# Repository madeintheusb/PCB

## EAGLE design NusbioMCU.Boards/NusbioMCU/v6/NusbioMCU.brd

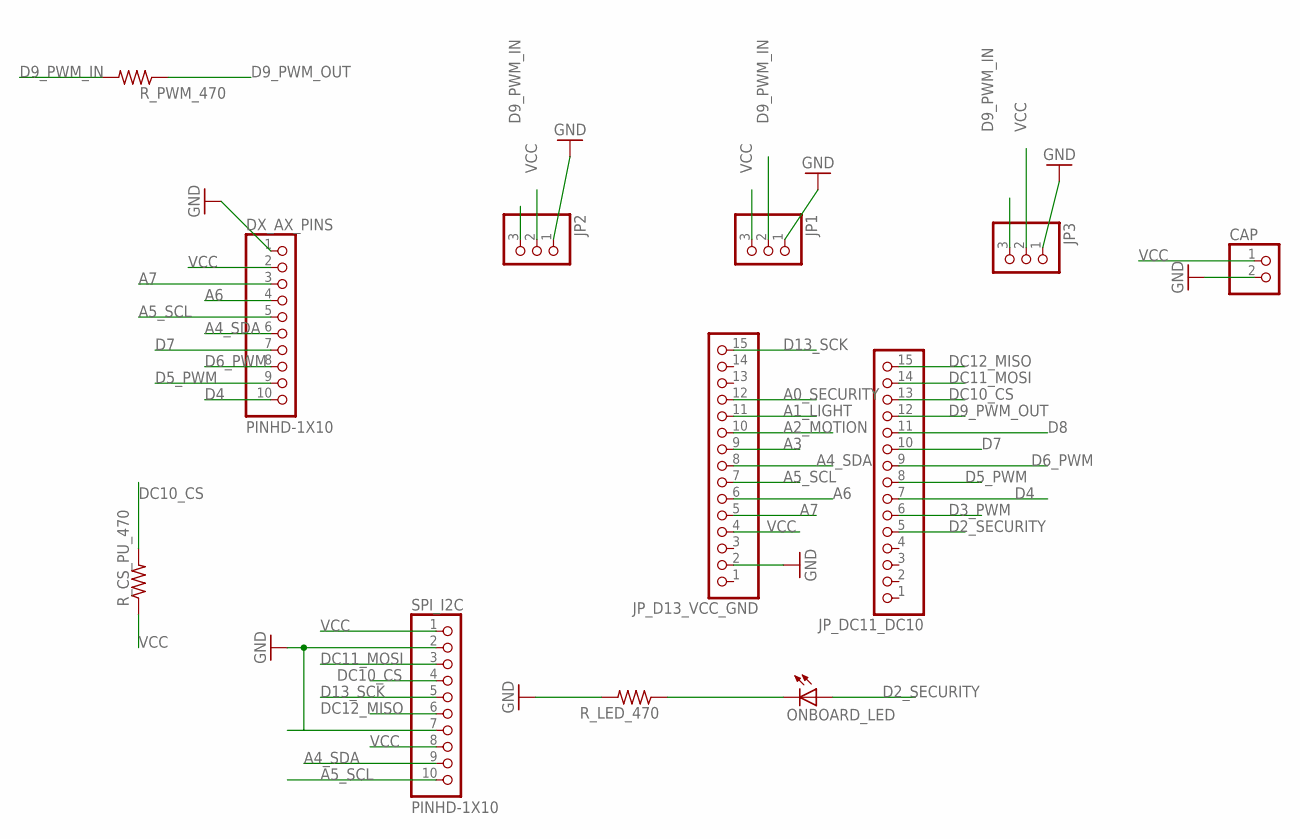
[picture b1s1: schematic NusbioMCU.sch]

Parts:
CAP: PINHD-1X2; 1X02
DX_AX_PINS: PINHD-1X10; 1X10-BIG
JP1, JP2, JP3: PINHD-1X3; 1X03
JP_D13_VCC_GND: PINHD-1X15; 1X15
JP_DC11_DC10: PINHD-1X15; 1X15
ONBOARD_LED: LEDSMT1206; 1206
R_CS_PU_470: R-US_R1206; R1206
R_LED_470: R-US_R1206; R1206
R_PWM_470: R-US_R1206; R1206
SPI_I2C: PINHD-1X10; 1X10-BIG

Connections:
A0_SECURITY: JP_D13_VCC_GND.12
A1_LIGHT: JP_D13_VCC_GND.11
A2_MOTION: JP_D13_VCC_GND.10
A3: JP_D13_VCC_GND.9
A4_SDA: DX_AX_PINS.6, JP_D13_VCC_GND.8, SPI_I2C.9
A5_SCL: DX_AX_PINS.5, JP_D13_VCC_GND.7, SPI_I2C.10
A6: DX_AX_PINS.4, JP_D13_VCC_GND.6
A7: DX_AX_PINS.3, JP_D13_VCC_GND.5
D2_SECURITY: JP_DC11_DC10.5, ONBOARD_LED.A
D3_PWM: JP_DC11_DC10.6
D4: DX_AX_PINS.10, JP_DC11_DC10.7
D5_PWM: DX_AX_PINS.9, JP_DC11_DC10.8
D6_PWM: DX_AX_PINS.8, JP_DC11_DC10.9
D7: DX_AX_PINS.7, JP_DC11_DC10.10
D8: JP_DC11_DC10.11
D9_PWM_IN: JP1.2, JP2.3, JP3.3, R_PWM_470.2
D9_PWM_OUT: JP_DC11_DC10.12, R_PWM_470.1
D13_SCK: JP_D13_VCC_GND.15, SPI_I2C.5
DC10_CS: JP_DC11_DC10.13, R_CS_PU_470.2, SPI_I2C.4
DC11_MOSI: JP_DC11_DC10.14, SPI_I2C.3
DC12_MISO: JP_DC11_DC10.15, SPI_I2C.6
GND: CAP.2, DX_AX_PINS.1, JP1.1, JP2.1, JP3.1, JP_D13_VCC_GND.2, R_LED_470.2, SPI_I2C.2, SPI_I2C.7
unnamed: ONBOARD_LED.C, R_LED_470.1
VCC: CAP.1, DX_AX_PINS.2, JP1.3, JP2.2, JP3.2, JP_D13_VCC_GND.4, R_CS_PU_470.1, SPI_I2C.1, SPI_I2C.8

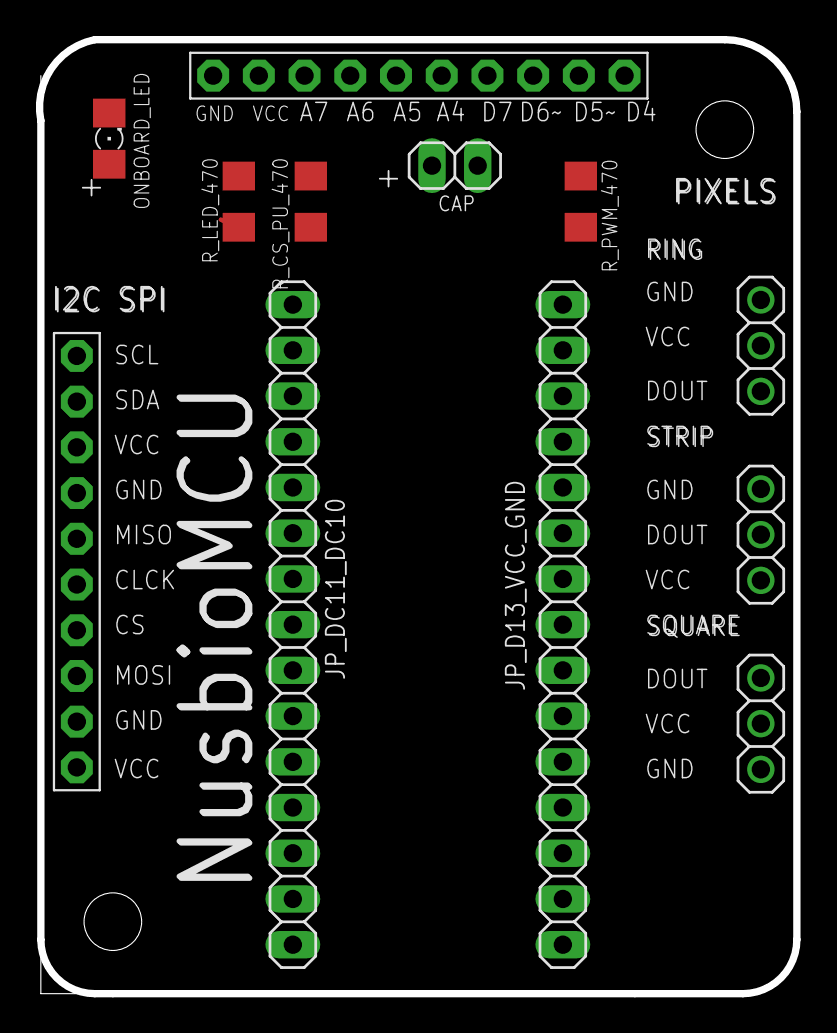
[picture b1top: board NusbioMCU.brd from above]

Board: 2 copper layers, 42.1 x 53.0 mm, 12 parts (0 on the bottom side), 18 nets.

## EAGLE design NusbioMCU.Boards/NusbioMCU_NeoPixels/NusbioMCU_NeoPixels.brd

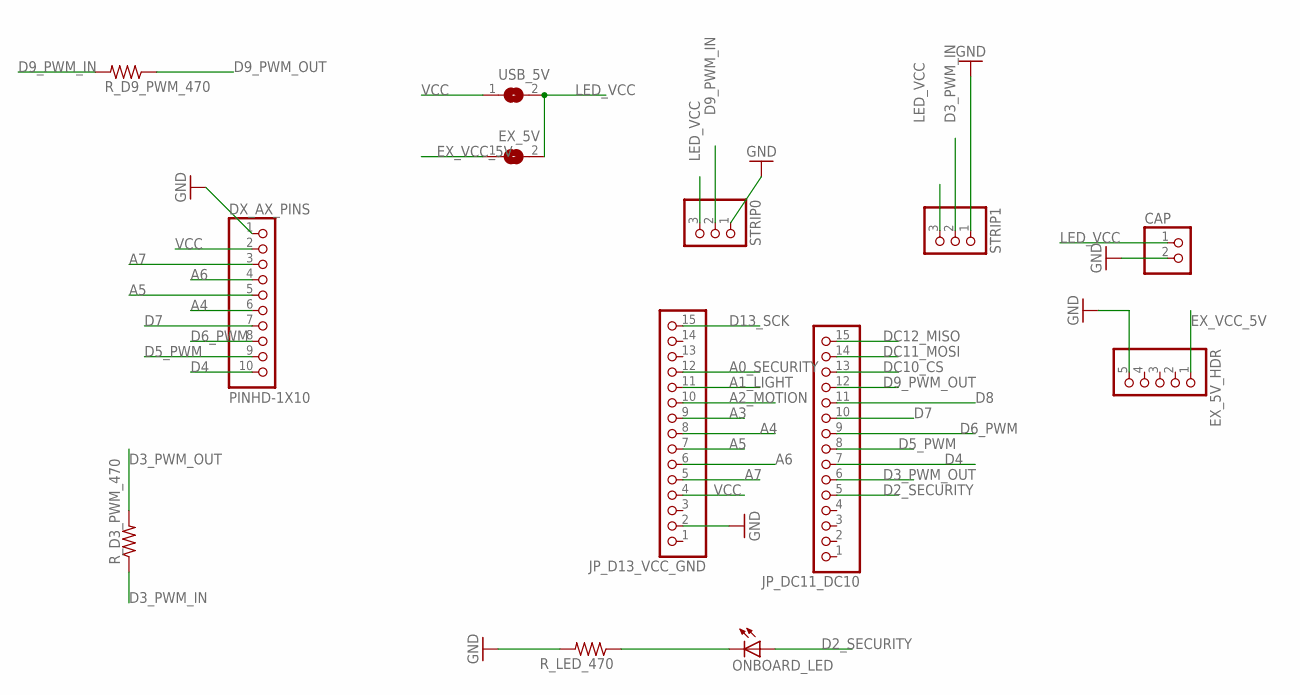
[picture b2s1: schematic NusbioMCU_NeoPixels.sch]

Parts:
CAP: PINHD-1X2; 1X02
DX_AX_PINS: PINHD-1X10; 1X10-BIG
EX_5V: SOLDERJUMPERREFLOW; SOLDERJUMPER_REFLOW
EX_5V_HDR: PINHD-1X5; 1X05
JP_D13_VCC_GND: PINHD-1X15; 1X15
JP_DC11_DC10: PINHD-1X15; 1X15
ONBOARD_LED: LEDSMT1206; 1206
R_D3_PWM_470, R_D9_PWM_470: R-US_R1206; R1206
R_LED_470: R-US_R1206; R1206
STRIP0, STRIP1: PINHD-1X3; 1X03
USB_5V: SOLDERJUMPERREFLOW; SOLDERJUMPER_REFLOW

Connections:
A0: JP_D13_VCC_GND.12
A1: JP_D13_VCC_GND.11
A2: JP_D13_VCC_GND.10
A3: JP_D13_VCC_GND.9
A4: DX_AX_PINS.6, JP_D13_VCC_GND.8
A5: DX_AX_PINS.5, JP_D13_VCC_GND.7
A6: DX_AX_PINS.4, JP_D13_VCC_GND.6
A7: DX_AX_PINS.3, JP_D13_VCC_GND.5
D2_SECURITY: JP_DC11_DC10.5, ONBOARD_LED.A; also elsewhere on the board
D3_PWM_IN: R_D3_PWM_470.1, STRIP1.2
D3_PWM_OUT: JP_DC11_DC10.6, R_D3_PWM_470.2
D4: DX_AX_PINS.10, JP_DC11_DC10.7
D5_PWM: DX_AX_PINS.9, JP_DC11_DC10.8
D6_PWM: DX_AX_PINS.8, JP_DC11_DC10.9
D7: DX_AX_PINS.7, JP_DC11_DC10.10
D8: JP_DC11_DC10.11
D9_PWM_IN: R_D9_PWM_470.2, STRIP0.2
D9_PWM_OUT: JP_DC11_DC10.12, R_D9_PWM_470.1
D13_SCK: JP_D13_VCC_GND.15
DC10_CS: JP_DC11_DC10.13
DC11_MOSI: JP_DC11_DC10.14
DC12_MISO: JP_DC11_DC10.15
EX_VCC_5V: EX_5V.1, EX_5V_HDR.1
GND: CAP.2, DX_AX_PINS.1, EX_5V_HDR.5, JP_D13_VCC_GND.2, R_LED_470.2, STRIP0.1, STRIP1.1
LED_VCC: CAP.1, EX_5V.2, STRIP0.3, STRIP1.3, USB_5V.2
unnamed 25: ONBOARD_LED.C, R_LED_470.1; also elsewhere on the board
VCC: DX_AX_PINS.2, JP_D13_VCC_GND.4, USB_5V.1

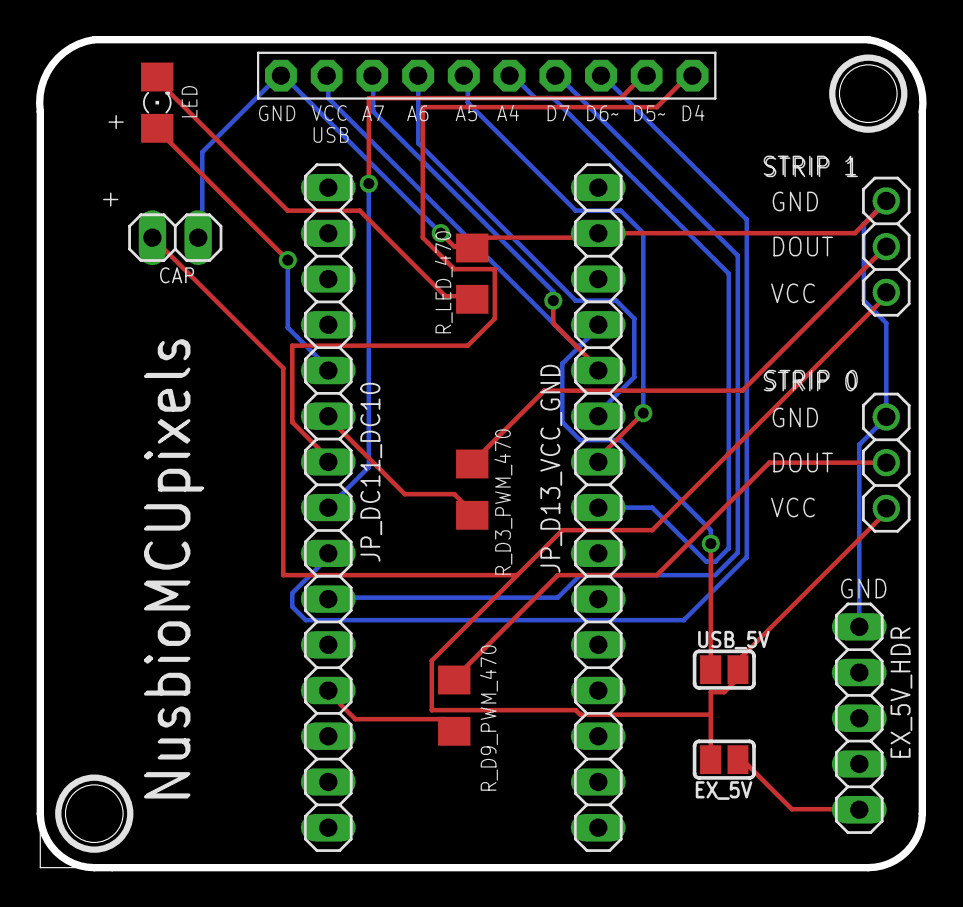
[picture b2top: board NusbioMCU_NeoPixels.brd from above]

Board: 2 copper layers, 49.1 x 46.0 mm, 13 parts (0 on the bottom side), 18 nets.

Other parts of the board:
LED: 1206

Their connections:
D2_SECURITY: LED.A; also elsewhere on the board
unnamed 25: LED.C; also elsewhere on the board

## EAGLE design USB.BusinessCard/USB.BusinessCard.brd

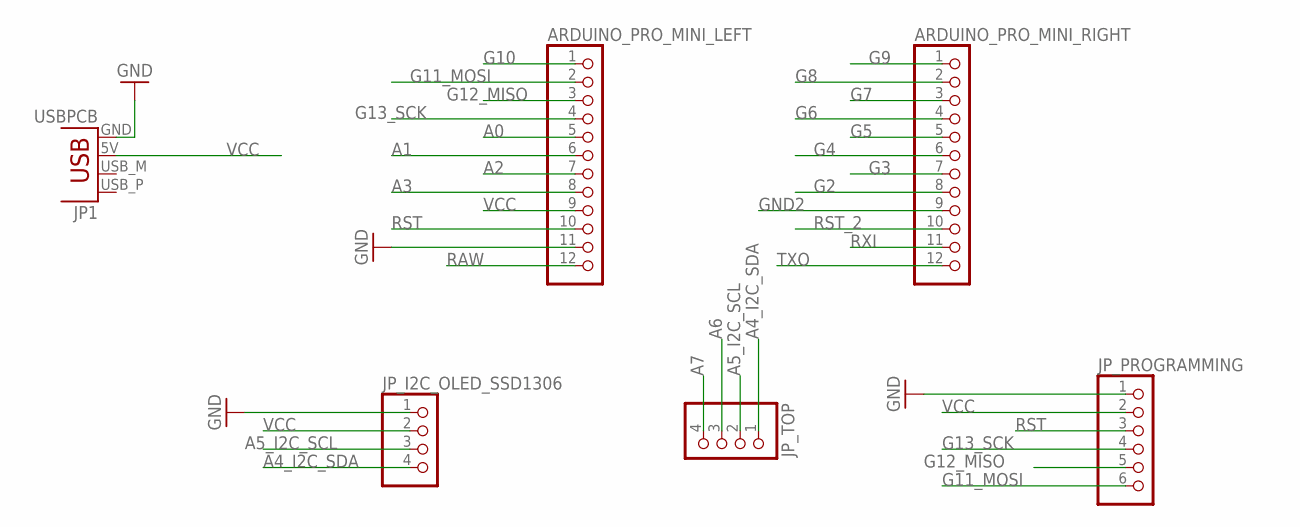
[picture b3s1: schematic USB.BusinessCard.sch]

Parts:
ARDUINO_PRO_MINI_LEFT: PINHD-1X12; 1X12
ARDUINO_PRO_MINI_RIGHT: PINHD-1X12; 1X12
JP1: USBPCB; USB-A-PCB
JP_I2C_OLED_SSD1306: PINHD-1X4; 1X04
JP_PROGRAMMING: PINHD-1X6; 1X06
JP_TOP: PINHD-1X4; 1X04

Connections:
A0: ARDUINO_PRO_MINI_LEFT.5
A1: ARDUINO_PRO_MINI_LEFT.6
A2: ARDUINO_PRO_MINI_LEFT.7
A3: ARDUINO_PRO_MINI_LEFT.8
A4_I2C_SDA: JP_I2C_OLED_SSD1306.4, JP_TOP.1
A5_I2C_SCL: JP_I2C_OLED_SSD1306.3, JP_TOP.2
A6: JP_TOP.3
A7: JP_TOP.4
G2: ARDUINO_PRO_MINI_RIGHT.8
G3: ARDUINO_PRO_MINI_RIGHT.7
G4: ARDUINO_PRO_MINI_RIGHT.6
G5: ARDUINO_PRO_MINI_RIGHT.5
G6: ARDUINO_PRO_MINI_RIGHT.4
G7: ARDUINO_PRO_MINI_RIGHT.3
G8: ARDUINO_PRO_MINI_RIGHT.2
G9: ARDUINO_PRO_MINI_RIGHT.1
G10: ARDUINO_PRO_MINI_LEFT.1
G11_MOSI: ARDUINO_PRO_MINI_LEFT.2, JP_PROGRAMMING.6
G12_MISO: ARDUINO_PRO_MINI_LEFT.3, JP_PROGRAMMING.5
G13_SCK: ARDUINO_PRO_MINI_LEFT.4, JP_PROGRAMMING.4
GND: ARDUINO_PRO_MINI_LEFT.11, JP1.GND, JP_I2C_OLED_SSD1306.1, JP_PROGRAMMING.1
GND2: ARDUINO_PRO_MINI_RIGHT.9
RAW: ARDUINO_PRO_MINI_LEFT.12
RST: ARDUINO_PRO_MINI_LEFT.10, JP_PROGRAMMING.3
RST_2: ARDUINO_PRO_MINI_RIGHT.10
RXI: ARDUINO_PRO_MINI_RIGHT.11
TXO: ARDUINO_PRO_MINI_RIGHT.12
VCC: ARDUINO_PRO_MINI_LEFT.9, JP1.5V (VBUS), JP_I2C_OLED_SSD1306.2, JP_PROGRAMMING.2

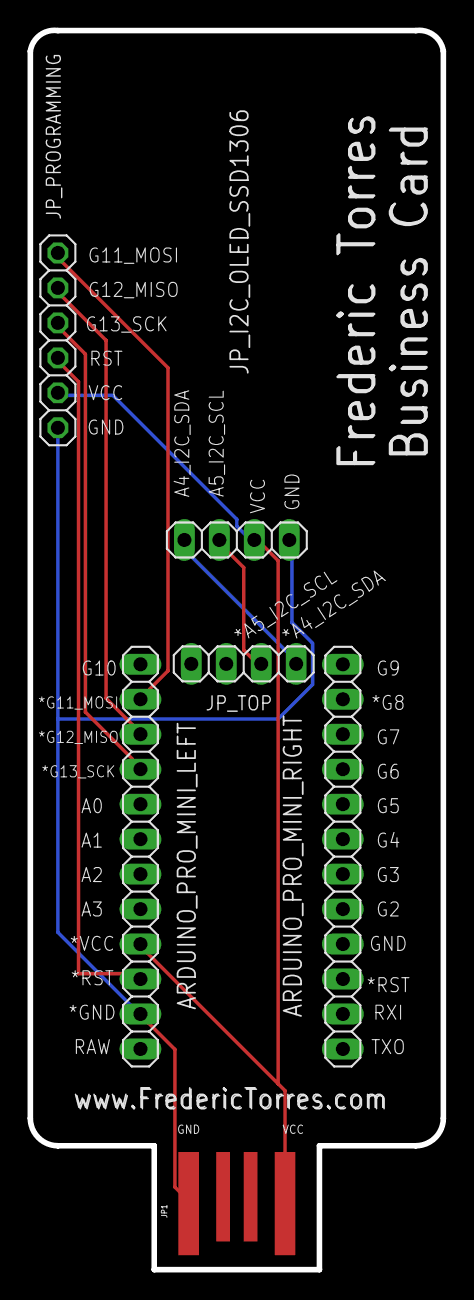
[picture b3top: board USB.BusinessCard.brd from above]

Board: 2 copper layers, 30.0 x 90.0 mm, 6 parts (0 on the bottom side), 8 nets.

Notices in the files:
parts and their libraries:
microbuilder: This work is placed in the public domain, and may be freely used for commercial and non-commercial work with the following conditions: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
SparkFun-Connectors: Licensing: Creative Commons ShareAlike 4.0 International - https://creativecommons.org/licenses/by-sa/4.0
